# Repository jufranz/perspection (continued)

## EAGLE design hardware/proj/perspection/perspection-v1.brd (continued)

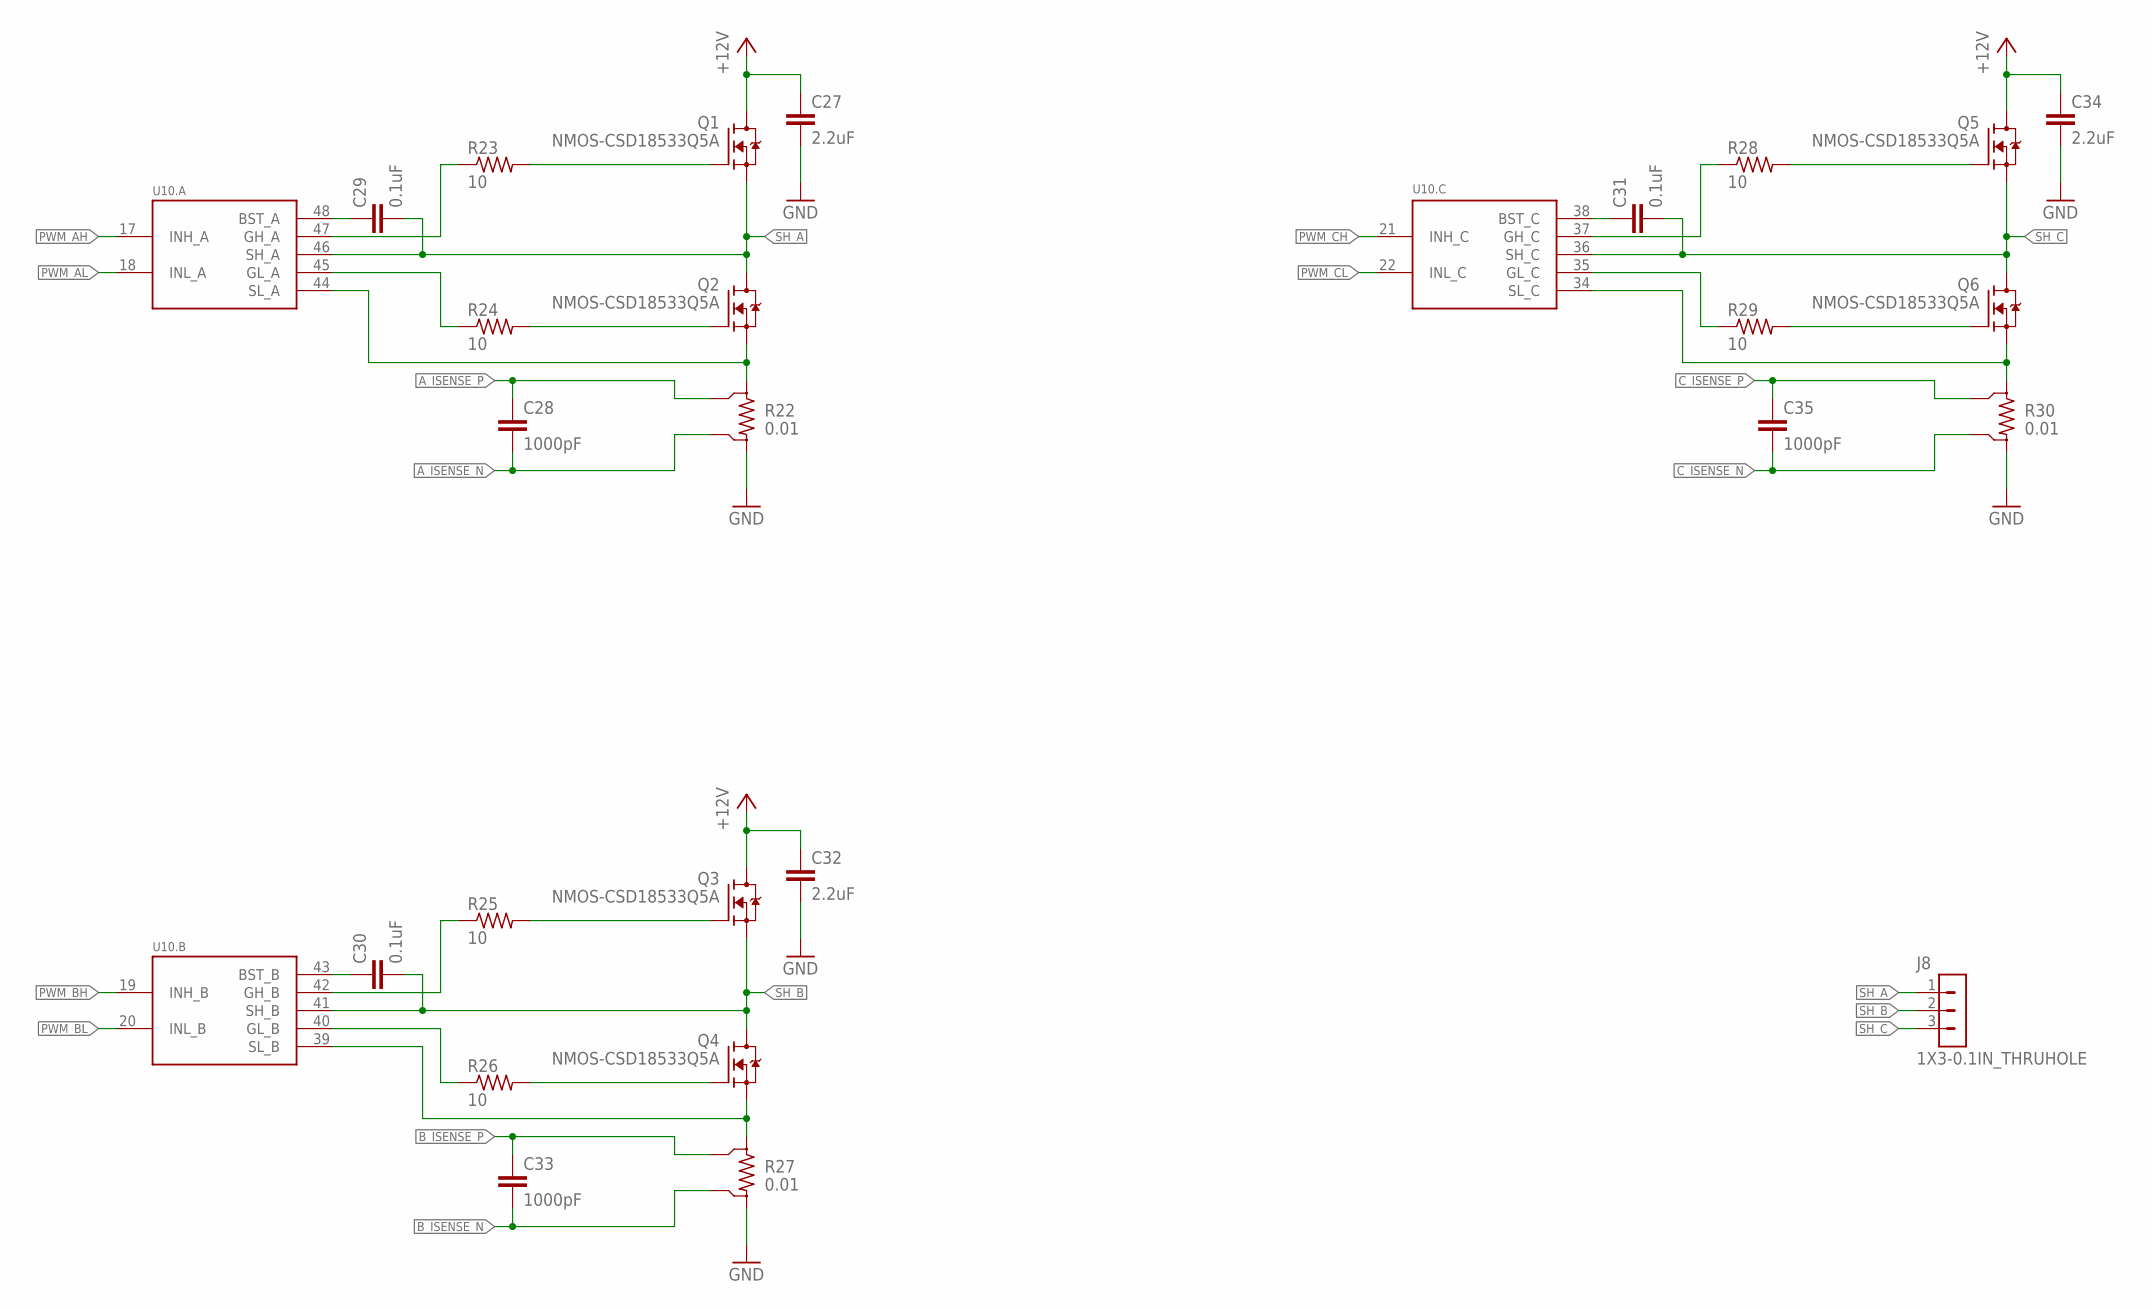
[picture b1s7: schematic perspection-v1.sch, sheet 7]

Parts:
C27, C32, C34: 2.2uF; C1210
C28, C33, C35: 1000pF; C0402
C29, C30, C31: 0.1uF; C0402
J8: 1X3-0.1IN_THRUHOLE; 1X3_0.1IN_THRUHOLE
Q1, Q2, Q3, Q4, Q5, Q6: NMOS-CSD18533Q5A; SON-5X6
R22, R27, R30: 0.01; R2010-4
R23, R24, R25, R26, R28, R29: 10; R0402
U10: DRV8301DCAR; TI-HTSSOP-56

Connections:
+12V: C27.1, C32.1, C34.1, Q1.D, Q3.D, Q5.D; also elsewhere on the board
A_ISENSE_N: C28.2, R22.V2 (S2); also elsewhere on the board
A_ISENSE_P: C28.1, R22.V1 (S1); also elsewhere on the board
B_ISENSE_N: C33.2, R27.V2 (S2); also elsewhere on the board
B_ISENSE_P: C33.1, R27.V1 (S1); also elsewhere on the board
C_ISENSE_N: C35.2, R30.V2 (S2); also elsewhere on the board
C_ISENSE_P: C35.1, R30.V1 (S1); also elsewhere on the board
GH_A: R23.1, U10.47 (GH_A)
GH_B: R25.1, U10.42 (GH_B)
GH_C: R28.1, U10.37 (GH_C)
GL_A: R24.1, U10.45 (GL_A)
GL_B: R26.1, U10.40 (GL_B)
GL_C: R29.1, U10.35 (GL_C)
GND: C27.2, C32.2, C34.2, R22.I2 (2), R27.I2 (2), R30.I2 (2); also elsewhere on the board
unnamed: C29.1, U10.48 (BST_A)
unnamed: Q3.G, R25.2
unnamed: Q1.G, R23.2
unnamed: Q2.G, R24.2
unnamed: Q4.G, R26.2
unnamed: Q5.G, R28.2
unnamed: Q6.G, R29.2
unnamed: C30.1, U10.43 (BST_B)
unnamed: C31.1, U10.38 (BST_C)
PWM_AH: U10.17 (INH_A); also elsewhere on the board
PWM_AL: U10.18 (INL_A); also elsewhere on the board
PWM_BH: U10.19 (INH_B); also elsewhere on the board
PWM_BL: U10.20 (INL_B); also elsewhere on the board
PWM_CH: U10.21 (INH_C); also elsewhere on the board
PWM_CL: U10.22 (INL_C); also elsewhere on the board
SH_A: C29.2, J8.1, Q1.S1 (S), Q1.S2 (S), Q1.S3 (S), Q2.D, U10.46 (SH_A); also elsewhere on the board
SH_B: C30.2, J8.2, Q3.S1 (S), Q3.S2 (S), Q3.S3 (S), Q4.D, U10.41 (SH_B); also elsewhere on the board
SH_C: C31.2, J8.3, Q5.S1 (S), Q5.S2 (S), Q5.S3 (S), Q6.D, U10.36 (SH_C); also elsewhere on the board
SL_A: Q2.S1 (S), Q2.S2 (S), Q2.S3 (S), R22.I1 (1), U10.44 (SL_A)
SL_B: Q4.S1 (S), Q4.S2 (S), Q4.S3 (S), R27.I1 (1), U10.39 (SL_B)
SL_C: Q6.S1 (S), Q6.S2 (S), Q6.S3 (S), R30.I1 (1), U10.34 (SL_C)

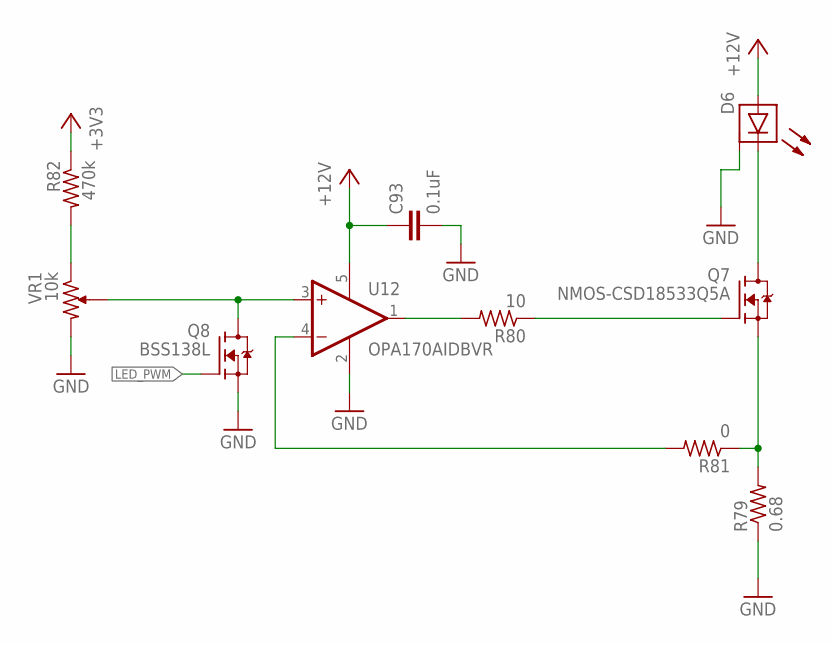
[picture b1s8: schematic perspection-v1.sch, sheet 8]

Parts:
C93: 0.1uF; C0402
D6: LED-PWR-XLAMP_MX3; XLAMP-MX3
Q7: NMOS-CSD18533Q5A; SON-5X6
Q8: BSS138L; SOT23
R79: 0.68; R0805
R80: 10; R0402
R81: 0; R0402
R82: 470k; R0402
U12: OPA170AIDBVR; SOT23-5
VR1: 10k; ST-4EA

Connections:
+3V3: R82.1; also elsewhere on the board
+12V: C93.1, D6.ANODE, U12.5 (V+); also elsewhere on the board
GND: C93.2, D6.THERM (HEAT), D6.THERM1 (HEAT), D6.THERM2 (HEAT), D6.THERM3 (HEAT), D6.THERM4 (HEAT), D6.THERM5 (HEAT), D6.THERM6 (HEAT), D6.THERM7 (HEAT), D6.THERM8 (HEAT), D6.THERM9 (HEAT), D6.THERM10 (HEAT), D6.THERM11 (HEAT), Q8.2 (S), R79.1, U12.2 (V-), VR1.3 (2); also elsewhere on the board
LED_PWM: Q8.1 (G); also elsewhere on the board
unnamed: D6.CATHODE, Q7.D
unnamed: Q7.S1 (S), Q7.S2 (S), Q7.S3 (S), R79.2, R81.1
unnamed: Q7.G, R80.1
unnamed: R81.2, U12.4 (-IN)
unnamed: R82.2, VR1.1
unnamed: Q8.3 (D), U12.3 (+IN), VR1.2 (WIPER)
unnamed: R80.2, U12.1 (OUT)

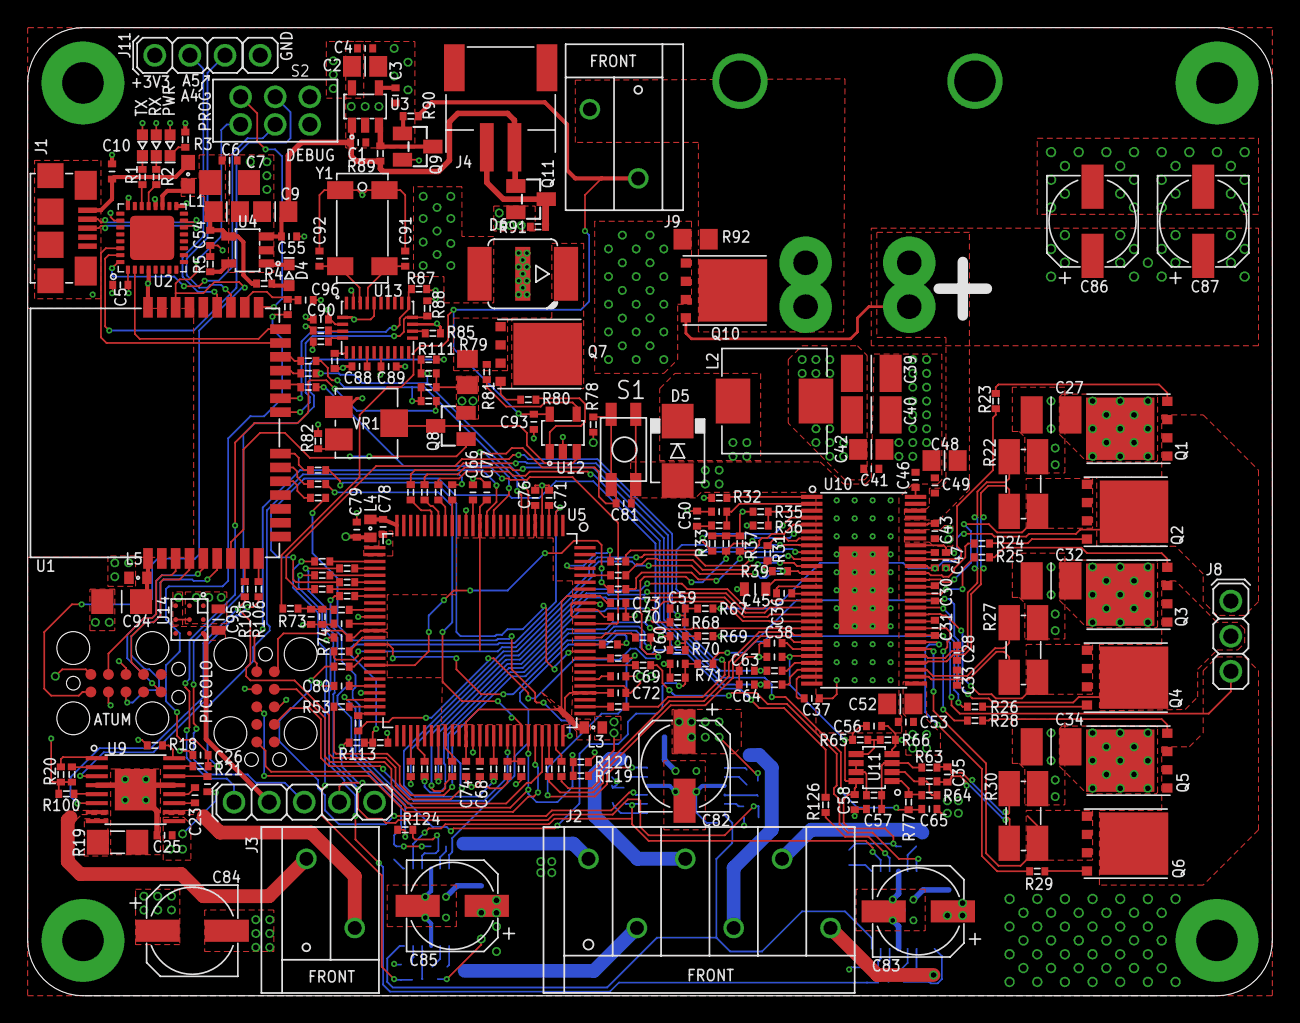
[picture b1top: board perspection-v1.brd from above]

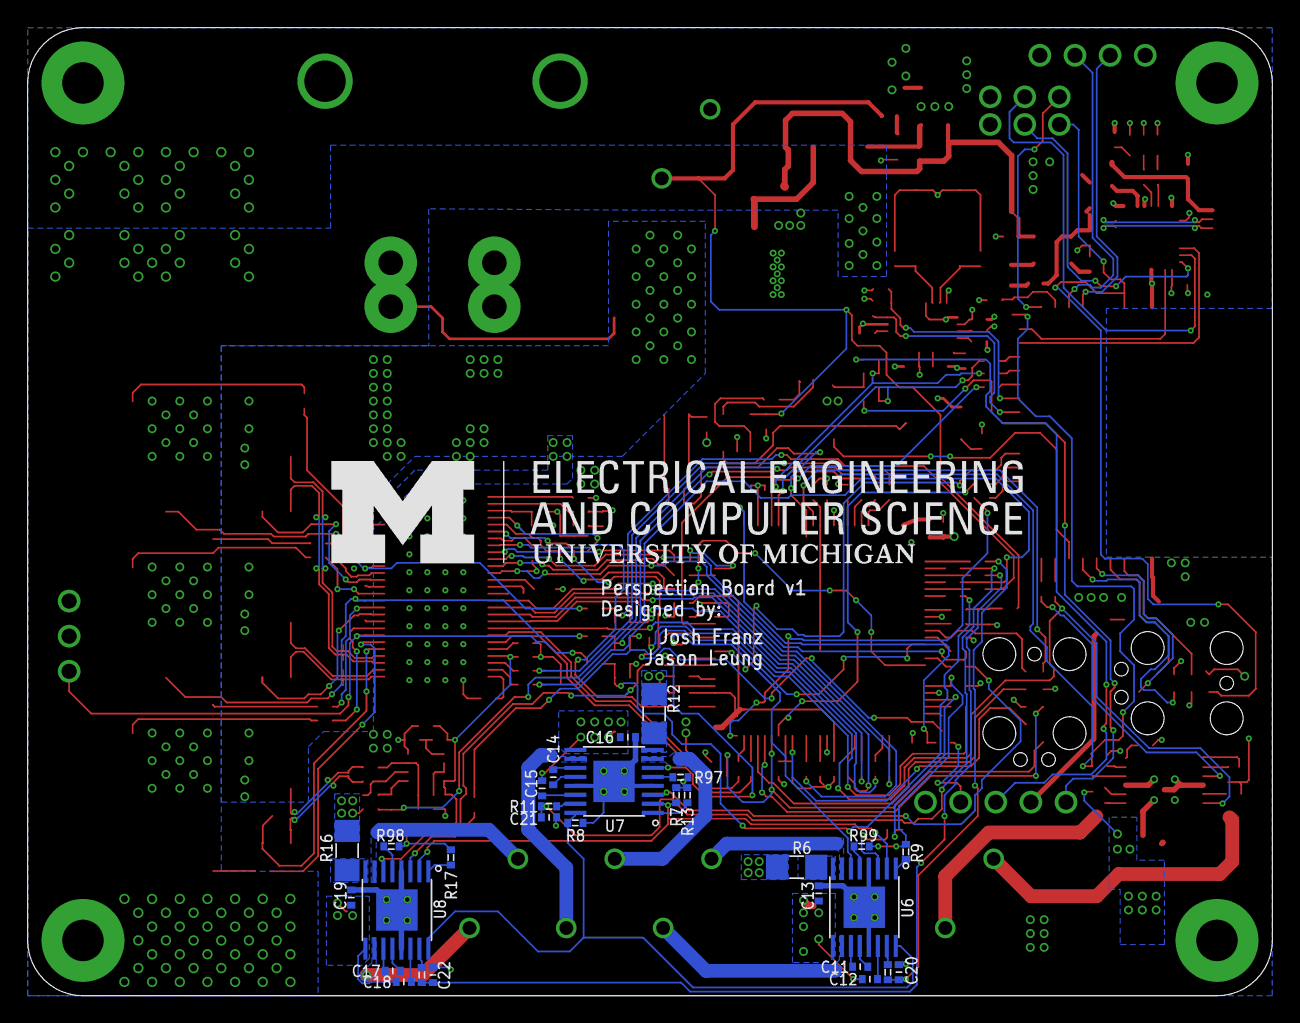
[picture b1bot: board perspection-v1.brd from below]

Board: 4 copper layers, 90.0 x 70.0 mm, 274 parts (30 on the bottom side), 239 nets.

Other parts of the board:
U$1: EECS_LOGO

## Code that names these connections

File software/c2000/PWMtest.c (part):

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//    Monitor ePWM1-ePWM3 pins on an oscilloscope as described
//    below.
//
//       EPWM1A is on GPIO0
//       EPWM1B is on GPIO1
//
//       EPWM2A is on GPIO2
//       EPWM2B is on GPIO3
//
//       EPWM3A is on GPIO4
//       EPWM3B is on GPIO5
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
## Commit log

2015-10-22 created repo, made parts, started perspection-rf schematic
2015-10-27 fixed gitignores, added hardware/software folders, added some handy dandy scripts
2015-10-27 fixed some script stuff and addex BMX055
2015-11-03 added mezzanine connector packages
2015-11-08 added contiki software stack! two submodules, contiki and cc2538-bsl. copied files from lab11/atum repo, with some modifications. Also updated gitignores
2015-11-10 i think i did something with stuff
2015-11-11 added atum board to library
2015-11-12 added 3d files for gimbal mounts
2015-11-12 added the C2000 processor and updated the get_digikey_data script to add a link to the Digi-key page
2015-11-12 updated piccolo device
2015-11-12 fixed LGA-20, added LGA-28 and BMO055, FTDI
2015-11-12 fucking changed Josh's script cuz it sucks and excludes the rest of the population from using his script properly cuz he's a poop
2015-11-12 josh is a poop
2015-11-12 added TPS54339, DRV8801, updated opamp symbols, fixed jason's shit
2015-11-13 added DRV8301 part. double check for connectivity
2015-11-13 added part info for DRV8301
2015-11-13 penis
2015-11-13 could only find through hole, smd not available
2015-11-13 quadrature decoding bitch. code needs to be cleaned though
2015-11-13 did too many things!
2015-11-13 Changed the quadrature device to use degrees instead of counts for position
2015-11-13 moved the haptics platform to just a perspection platform, fixed the degrees-based quadrature shit
2015-11-13 UMich logos
2015-11-14 removed old boards, started new board, did lots of shit
2015-11-14 added script to convert dxfs to polygons. useful for logos. also added high power led, fet, and something else i can't remember
2015-11-14 test ancestory commit
2015-11-14 test branch commit
2015-11-14 test local commit
2015-11-14 another test
2015-11-14 ready to merge back into pcb
2015-11-14 changed power LED
2015-11-14 added BSS138L
2015-11-14 fixed digikey data parsing with unicode, added some parts
2015-11-15 finished piccolo stuff, for the most part
2015-11-15 added button and switch from Atum
2015-11-15 added OPA170
2015-11-15 parts and LED circuit and shit
2015-11-15 started led thing
2015-11-15 added aluminum bulk caps
2015-11-15 new connector under 1x2 called MOLEX_SABR_...E
2015-11-15 i dont fuckin kno what i did
2015-11-15 finished them dots
2015-11-15 Changed the quadrature device to polling-based
2015-11-15 Got rid of the LED toggling in the quadrature device
2015-11-16 boz is making me commit
2015-11-16 TAKE THIS SHIT JASON
2015-11-16 PWM for days
2015-11-16 I have no idea what's going on with torque control
2015-11-16 holy fucking shit 81 airwires to go
2015-11-16 small change. holy fucking shit so tight
2015-11-16 1x4 header fucking yeah
2015-11-16 boost converter triple checked
2015-11-16 26 airwires!
2015-11-17 no airwires! for now...
2015-11-17 JASON TAKE THE WHEEL
2015-11-17 test point
2015-11-17 blarg
2015-11-17 dobule blarg
2015-11-17 Kinda sorta torque control is working
2015-11-17 Wtf torque controler
2015-11-17 pretty much done, need to compile BOM
2015-11-17 silkscreeeeen
2015-11-17 added 4 pin connector, cleaned up test layer, added block diagram, changed GVDD cap to a larger package for higher voltage rating, removed unused cam files, added our own cam processor, added LED_PWM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
2015-11-17 blah
2015-11-17 ORDER THIS SHIT
2015-11-17 fixed fuckups sorry bros
2015-11-18 no board changes. gave every net a class related to its voltage, and created a script to assign a voltage attribute to every capacitor.
2015-11-18 did the same thing, but for this branch. we will see how the merge goes...
2015-11-19 stuff i forgot to commit that is trivial
2015-11-19 fixed stub (!!), set resistor values for LED driver and updated part numbers accordingly
2015-11-19 UGH JASON STOP USING THE FUCKING PCB BRANCH
2015-11-19 New stuff from contiki
2015-11-19 fuck business
2015-11-20 Testing some quadrature shit
2015-11-20 FUCKING ORDER SHIT
2015-11-20 Create PWMtest.c
    Test code for PWM for C2000 Launchpad
2015-11-20 Made a c2000 folder under software
2015-11-21 Yay c2000 quadrature
    And standalone CCS6 projects!
2015-11-21 C2000 PWM is up and running, just needs edits to make it more flexible
    Also, made a local copy of hal.c for this project because it was fucking
    with the PWM
2015-11-22 haven't actually tested anything but the new C2000 pwm shit looks better and builds so we're gonna roll with it
2015-11-22 ADC for days and days
2015-11-23 fuck everything
2015-11-23 most of torque control running on c2000
2015-11-23 needs tuning but torque control on c2000 is running
2015-11-23 mmmf dat torque control doe
2015-11-24 added i2c-test, confirmed it can communicate with IMU. added I2C pins to board.h
2015-11-24 maybe updating contiki library might fix shit?
2015-11-25 Added BNO055 driver (needs more testing), made bno055-test to spew imu data over serial
2015-11-25 wtf contiki
2015-11-29 SPIslave files
    Files for SPI slave functionality, readme included
2015-11-29 spi-test
2015-11-30 atum spi wrappers
2015-11-30 spi-test works
2015-11-30 Rudimentary versions of the camera and headset apps
2015-11-30 fixes for spi
    fixed spi stuff
2015-12-01 communications test folder
2015-12-01 Made a CCS project that's almost completely independent of the motorware installation
2015-12-01 I don't know what happened but now it works
2015-12-01 Cleaning HAL and SPI stuff up
2015-12-01 Forgot what changed, too lazy to look at diff
2015-12-01 SPI slave stuff works with instaspin motion (lab 13a)
2015-12-01 changes to the thing
2015-12-01 added communications library for perspection system. needs work on IMU part, but robot movement control is all working for testing purposes
2015-12-01 Cleaning HAL and library stuff up a bit
2015-12-01 lol whoops turns out all of the important stuff was being gitignored
2015-12-02 hardcoding most of the stuff to use J5
2015-12-02 motor control stuff in HAL except for torque feedback
2015-12-02 yay spinning robot
2015-12-02 robot-code will be directory for all codes running on robot that is atum and(?) c2000
2015-12-02 Added SPI stuff
2015-12-02 remote control is almost working but spi is fucky
2015-12-03 added robot direction heading code for controller
2015-12-03 Atum SPI stuff
2015-12-03 spi tests on johns computer
    d
2015-12-03 spyyyyy
2015-12-04 Atum SPI wrapper
2015-12-04 robit
2015-12-04 ribbit
2015-12-04 aayyyydc
2015-12-04 Adding SPI protocol stuff into the HAL shit
2015-12-04 modified comms code
2015-12-04 unfucked the c2000 build
2015-12-04 actually unfucked the build now
2015-12-04 made separate c2000 projects for each board
2015-12-05 Fixed some shiz
2015-12-05 c2000 robot body code integrate with gimbal position control -- careful running this
2015-12-05 changed body and controller atum code to include gimbal pos control
2015-12-05 looks... ok
2015-12-06 headset test
2015-12-06 Added scissorMotorControl to movement_recv
2015-12-06 readd scissor.c back into makefile, and in body.c i commented it out because it wasn't ready yet
2015-12-06 CALIBRATION
2015-12-06 updated comms library. should be final iteration. read documentation carefully. also cleaned up headset code
2015-12-06 cleaned up code and added example stuff in body.c for you guys to fuck around with
2015-12-06 cleaned up shit and made it fucking sexy
2015-12-06 moved delay to clock_wrapper, changed delay() clock_wrapper_delay_msec for sake of function naming convention
2015-12-06 made delay between calibration process and obtain orientation process 750 millisecs
2015-12-06 jk i want to make it fucking 1000 milliseconds
2015-12-06 made pretty colors and coordinated between devices
2015-12-06 made pretty blinking sequences
2015-12-06 Cleaned up the robot-code, just formatting stuff
2015-12-06 added scissor control back
2015-12-06 Added dev/pwm.h
2015-12-06 Also cleaned up comms
2015-12-06 small clean up
2015-12-06 Cleaning stuff
2015-12-06 added scissor code
2015-12-06 working on comms, just gotta pull right now;
2015-12-06 First draft of all of the comms stuff
2015-12-07 Added scissor.c to Perspection makefile
2015-12-07 baseline wireless comms are working
2015-12-07 Moving around user_j5 files to the right places
2015-12-07 Added cad files to hardware folder
2015-12-07 C2000 crap for gimbal stuff
2015-12-07 Getting gimbal data stuff working between headset and robot body
2015-12-08 know whats better than one axis? two axes at the same time.
2015-12-08 added show-values.ulp and Arduino folder
2015-12-08 moved Arduino folder
2015-12-08 added beeping
2015-12-08 switched to built in tone library to generate 4kHz and 5kHz tones. Also added an enabled variable to allow the system to be off but not in fault
2015-12-08 renamed the top-level apps folder to ios
2015-12-08 soft limits on the gimbal on the atum side of things
2015-12-08 soft limits on the gimbal on the c2000 side of things
2015-12-08 Flash programming working, added debug leds
2015-12-09 added QEP interrupt
2015-12-09 dont use this for real things, trying to fix spi
2015-12-09 something changed with the apps
2015-12-09 spys are fixed
2015-12-09 changed check freq to 256, bc 2.4 is sluttier than your ex
2015-12-09 blehhhhhhhh
2015-12-09 kill switch works
2015-12-09 created knob and shaft adapter STLs
2015-12-10 fuck everything screw shit everywhere
2015-12-10 shaft adapter v2
2015-12-10 wrapped up the zeroing stuff
2015-12-10 shaft adapter v2 v2
2015-12-10 fucked with shit
2015-12-10 putting in the code for the fancy controller
2015-12-10 final edits for demo
2015-12-14 fixed a silly bug in the c2000 spi interrupt
2015-12-15 haptics
2015-12-16 rotational control! better control!
2015-12-16 yay it turns
2016-05-18 fixed get_digikey_data
